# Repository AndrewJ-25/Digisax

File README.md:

# STARLITE

## Description
STARLITE is a minimalist Digital Saxophone (Digisax) controlled by ESP32-S3.

### Inspiration
This project is intended to be a cost effective, customisable alternative to commercially available wind synths. STARLITE can be used for both performance and silent practice. It weds my two favorite hobbies: music and tinkering.

### Features:
- realistic ergonomics
- UI in the form of an OLED display and rotary encoder, to control master volume and timbre
- differential pressure sensor for responsive breath control
- pressure tube and bleed tube to simulate realistic resistance to blowing
- audio synthesised locally
- 3x7 key matrix featuring MX Black switches
- power via 5V barrel jack
- DAC with headphone output

The neck can be blown into directly, but an alto saxophone mouthpiece is recommended. (Not included in this project.)

OnShape link: https://cad.onshape.com/documents/a64dba8dfd86a5efa1851173/w/8b62b2d00aa632cf961d9b4c/e/8ecfcb79b78c17c244b3f0aa

## Schematic and PCB

A pdf version can be found under pcb/unconnected_pcb.

PCB front

PCB back

NOTE: Kicad project contatining an unconnected, partially routed pcb can be found under pcb/unconnected_pcb. A fully routed, panelised pcb can be found under pcb/panelised_pcb. Gerber files were generated from the latter.

## Assembly
1. All parts can be handsoldered. I recommend soldering the key-switches last.
2. 3D printed parts to contain M3 heatset inserts.
3. Cut two lengths of food grade silicone tubing, 70mm (pressure tube) and 240mm (bleed tube) in length.
4. All plumbing is a push fit. Connect the pressure tube between the neck and pressure sensor. Bleed tube carries condensation from the neck to the bottom of the instrument. Holes in the right-hand-pinky-keys can hold the bleed tube in place.
5. All keycaps are a push fit. See images at bottom of page for correct placement.
6. Wrap cork around the neck to ensure an airtight fit with the mouthpiece.

3D printed parts:

|Quantity|Description|
|-|-|
|1|key B|
|1|key B-flat|
|1|key C-sharp|
|1|key G-sharp|
|3|key left palm|
|1|key low B flat|
|1|key Octave|
|3|key right palm|
|2|key right pinky|
|7|key round|
|1|mount left|
|1|mount left palm|
|1|mount left pinky|
|2|mount right palm|
|2|mount right pinky|

## BOM
|Quantity|Total cost/GBP|Description|MPN|Suggested source|
|-|-|-|-|-|
|1|16.88|PCB|-|https://jlcpcb.com/|
|1|6.30|DAC amplifier|Adafruit TLV320DAC3100 breakout board|https://thepihut.com/products/adafruit-tlv320dac3100-i2s-dac-with-headphone-and-speaker-out|
|1|10.40|MCU|ESP32-S3-DevKitC-1|https://www.aliexpress.com/item/1005009298826918.html|
|1|5.73|Differential pressure sensor|MPXV7007DP|https://www.aliexpress.com/item/1005009368234291.html|
|1|1.43|I2C ADC|MCP3221|https://www.mouser.co.uk/ProductDetail/Microchip-Technology/MCP3221A7T-E-OT?qs=uHi2%2FQoPa5B%2FLE1GKuvdgg%3D%3D|
|21|23.49 (30pcs)|Keyboard switches|Cherry MX Black|https://www.ebay.co.uk/itm/203537430495?_skw=mx+black+switch|
|1|3.80|0.91" OLED display|SSD1306|https://www.aliexpress.com/item/1005006365845676.html|
|1|1.16|rotary encoder|EC11|https://www.aliexpress.com/item/1005005983134515.html|
|1|0.80|Barrel jack|DC-005|https://www.aliexpress.com/item/4001206395694.html|
|21|2.27|Diode|1N4148|https://www.aliexpress.com/item/1005010526571917.html|
|4|3.00|Capacitors|470pF, 100nF, 470uF|https://www.digikey.co.uk/|
|29|5.75 (50 pcs)|Screw M3|M3 * 12 Phillip's head|https://www.ebay.co.uk/itm/221326204336|
|29|8.88 (100 pcs)|Heat-set insert M3|M3 * 4 * 4.5|https://www.ebay.co.uk/itm/376068195160|
|1|3.20|Food grade silicone hose|ID 3mm OD 5mm length 1mm|https://www.ebay.co.uk/itm/227352704780?var=526554578797|
|1|5.44|cork sheet|~2mm thickness|https://www.ebay.co.uk/itm/277911247699|
|-|10|3D printed parts|-|-|
|TOTAL|108.53|-|-|-|

## Code

Firmware is written in C++.

Column pins use the ESP-32's internal pullup, and all row pins are set to high. I implemented a loop where all the rows are pulled high by default, and any column which is detected as low is matched with the key's corresponding row.

At the moment the code detects simultaneous key presses and prints the note which the current fingering corresponds to. Matrix and fingering mappings can be found in the code/ directory.

Note synthesis and volume control via the rotary encoder will be implemented once the project is built.

```cpp
#include <Arduino.h>
#include <map>
#include <initializer_list>

// =====================
// MATRIX PINS
// =====================

int Rows[] = {7, 15, 16, 17, 18, 8, 9};
int Columns[] = {10, 11, 12};

// =====================
// KEY NAMES
// =====================

const char* saxKey[7][3] =
{
    {"Octave1","L1","Ls1"},
    {"fork1","Bf1","Ls2"},
    {"Rs1","L2","Ls3"},
    {"Rs2","L3","Gsh1"},
    {"Rs3","R1","Csh1"},
    {"Dsh1","R2","LB1"},
    {"C1","R3","LBf1"}
};

// =====================
// BIT POSITIONS
// =====================

enum KeyBits
{
    OCTAVE1,
    L1,
    LS1,
    FORK1,
    BF1,
    LS2,
    RS1,
    L2,
    LS3,
    RS2,
    L3,
    GSH1,
    RS3,
    R1,
    CSH1,
    DSH1,
    R2,
    LB1,
    C1,
    R3,
    LBF1
};

// =====================
// KEY -> BIT LOOKUP
// =====================

std::map<String, uint8_t> keyToBit =
{
    {"Octave1", OCTAVE1},
    {"L1", L1},
    {"Ls1", LS1},
    {"fork1", FORK1},
    {"Bf1", BF1},
    {"Ls2", LS2},
    {"Rs1", RS1},
    {"L2", L2},
    {"Ls3", LS3},
    {"Rs2", RS2},
    {"L3", L3},
    {"Gsh1", GSH1},
    {"Rs3", RS3},
    {"R1", R1},
    {"Csh1", CSH1},
    {"Dsh1", DSH1},
    {"R2", R2},
    {"LB1", LB1},
    {"C1", C1},
    {"R3", R3},
    {"LBf1", LBF1}
};

// =====================
// FINGERING TABLE
// =====================

std::map<uint32_t, float> waves;

// =====================
// CREATE BITMASK
// =====================

uint32_t makeMask(std::initializer_list<uint8_t> keys)
{
    uint32_t mask = 0;

    for(auto key : keys)
    {
        mask |= (1UL << key);
    }

    return mask;
}

// =====================
// SETUP
// =====================

void setup()
{
    Serial.begin(115200);

    // Row pins output
    for(int i = 0; i < 7; i++)
    {
        pinMode(Rows[i], OUTPUT);
        digitalWrite(Rows[i], HIGH);
    }

    // Column pins input pullup
    for(int i = 0; i < 3; i++)
    {
        pinMode(Columns[i], INPUT_PULLUP);
    }

    // =====================
    // NOTE TABLE
    // =====================

    waves[makeMask({L1,L2,L3,R1,R2,R3,C1,LBF1})] = 138.59;
    waves[makeMask({L1,L2,L3,R1,R2,R3,C1,LB1})]  = 146.83;
    waves[makeMask({L1,L2,L3,R1,R2,R3,C1})]      = 155.56;
    waves[makeMask({L1,L2,L3,R1,R2,R3,C1,CSH1})] = 164.81;
    waves[makeMask({L1,L2,L3,R1,R2,R3})]         = 174.61;
    waves[makeMask({L1,L2,L3,R1,R2,R3,DSH1})]    = 185.00;
    waves[makeMask({L1,L2,L3,R1,R2})]            = 196.00;
    waves[makeMask({L1,L2,L3,R1})]               = 207.65;
    waves[makeMask({L1,L2,L3,R2})]               = 220.00;
    waves[makeMask({L1,L2,L3})]                  = 233.08;
    waves[makeMask({L1,L2,L3,GSH1})]             = 246.94;
    waves[makeMask({L1,L2})]                     = 261.63;
    waves[makeMask({L1,BF1})]                    = 277.18;
    waves[makeMask({L1})]                        = 293.66;
    waves[makeMask({L2})]                        = 311.13;
    waves[makeMask({})]                          = 329.63;

    Serial.println("Digital Sax Ready");
}

// =====================
// LOOP
// =====================

void loop()
{
    uint32_t currentMask = 0;

    // Scan all rows
    for(int row = 0; row < 7; row++)
    {
        // Disable all rows
        for(int r = 0; r < 7; r++)
        {
            digitalWrite(Rows[r], HIGH);
        }

        // Activate one row
        digitalWrite(Rows[row], LOW);

        delayMicroseconds(50);

        // Read columns
        for(int col = 0; col < 3; col++)
        {
            if(digitalRead(Columns[col]) == LOW)
            {
                const char* keyName = saxKey[row][col];

                currentMask |=
                    (1UL << keyToBit[String(keyName)]);

                Serial.print("Pressed: ");
                Serial.println(keyName);
            }
        }
    }

    // Lookup note
    auto note = waves.find(currentMask);

    if(note != waves.end())
    {
        Serial.print("Frequency: ");
        Serial.println(note->second);
    }
    else
    {
        Serial.println("Unknown fingering");
    }

    Serial.println("----------------");

    delay(50);
}
```

## More images

## Acknowledgements <3

Massive thank you to Rehan for sacrificing his sleep to write the firmware.

Also to Sua for designing a BANGING zine.

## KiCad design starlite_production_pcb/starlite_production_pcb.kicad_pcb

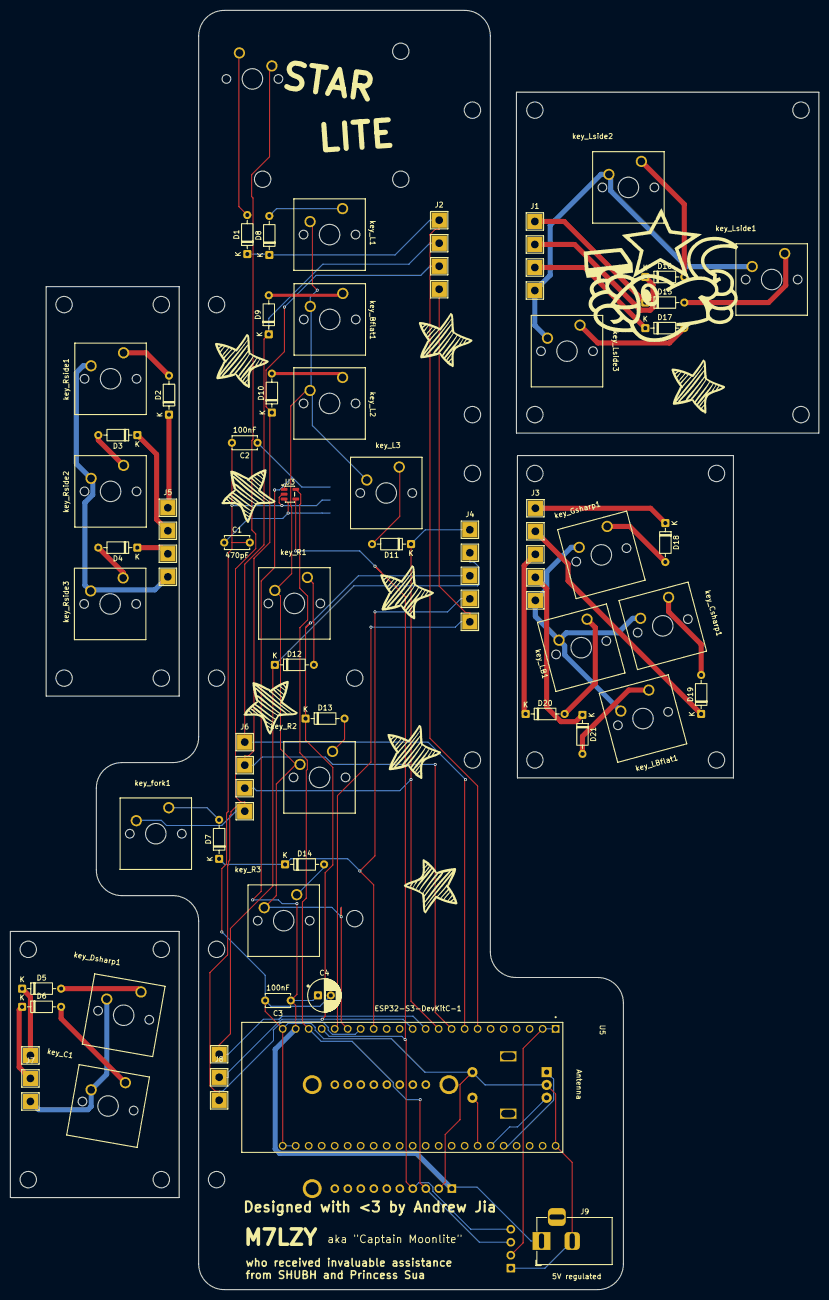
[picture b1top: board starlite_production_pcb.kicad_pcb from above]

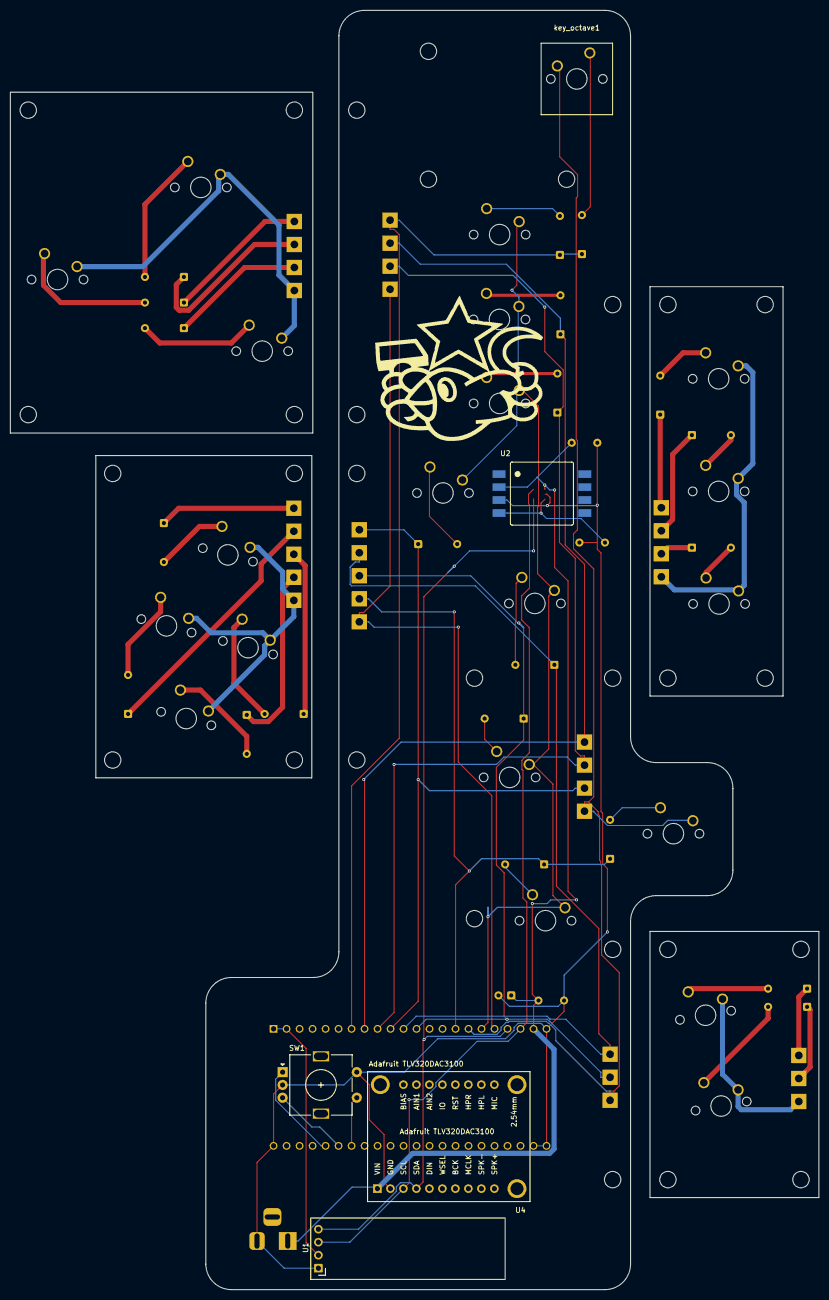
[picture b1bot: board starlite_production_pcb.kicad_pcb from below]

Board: 2 copper layers, 158.0 x 250.0 mm, 90 parts (5 on the bottom side), 56 nets.

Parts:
C1: 470pF; C_Disc_D4.7mm_W2.5mm_P5.00mm
C2, C3: 100nF; C_Disc_D4.7mm_W2.5mm_P5.00mm
C4: 470uF; CP_Radial_D6.3mm_P2.50mm
D1, D2, D3, D4, D5, D6, D7, D8, D9, D10, D11, D12, D13, D14, D15, D16, D17, D18, D19, D20, D21: 1N4148; D_DO-35_SOD27_P7.62mm_Horizontal
J1, J2, J5, J6: Conn_01x04_Pin; pad_1x4
J3, J4: Conn_01x05_Pin; pad_1x5
J7, J8: Conn_01x03_Pin; pad_1x3
J9: Barrel_Jack; BarrelJack_Horizontal
SW1: RotaryEncoder_Switch; RotaryEncoder_Alps_EC11E-Switch_Vertical_H20mm
U1: ER_OLEDM0.91_1x-I2C
U2: MPXV7007; MPXV7007DP
U3: MCP3221; SOT-23-5
U4: TLV320DAC3100_breakout; adafruit_TLV320DAC3100
U5: ESP32-S3; ESP32-S3-DevKitC-1
h1, h2, h3, h4, h5, h6, h7, h8, h9, h10, h11, h12, h13, h14, h16, h17, h18, h19, h20, h21, h22, h23, h24, h25: MountingHole_3.2mm_M3
key_Bflat1: SW_Push; slim_switch
key_C1: SW_Push; slim_switch
key_Csharp1: SW_Push; slim_switch
key_Dsharp1: SW_Push; slim_switch
key_Gsharp1: SW_Push; slim_switch
key_L1, key_L2, key_L3: SW_Push; slim_switch
key_LB1: SW_Push; slim_switch
key_LBflat1: SW_Push; slim_switch
key_Lside1, key_Lside2, key_Lside3: SW_Push; slim_switch
key_R1, key_R2, key_R3: SW_Push; slim_switch
key_Rside1, key_Rside2, key_Rside3: SW_Push; slim_switch
key_fork1: SW_Push; slim_switch
key_octave1: SW_Push; slim_switch
neck1, neck2, neck3: MountingHole_3.2mm_M3
thumb1, thumb2: MountingHole_3.2mm_M3

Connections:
+3.3V: U1.2 (VCC), U5.1 (3V3), U5.2 (3V3)
+5V: C2.1, C3.1, C4.1, J9.1, U2.2 (Vcc), U3.1 (V_{DD}), U4.1 (VIN), U5.21 (5V0)
EC11_A: SW1.A, U5.27 (GPIO2)
EC11_B: SW1.B, U5.28 (GPIO42)
EC11_button: SW1.S1, U5.29 (GPIO41)
GND: C1.2, C2.2, C3.2, C4.2, J9.2, SW1.C, SW1.S2, U1.1 (GND), U2.3 (GND), U3.2 (V_{SS}), U4.2 (GND), U5.22 (GND), U5.23 (GND), U5.43 (GND), U5.44 (GND)
I2C_SCL: U1.3 (SCL), U3.5 (SCL), U4.3 (SCL), U5.20 (GPIO14)
I2C_SDA: U1.4 (SDA), U3.4 (SDA), U4.4 (SDA), U5.19 (GPIO13)
unnamed: D1.2 (A), key_octave1.1
unnamed: D2.2 (A), key_Rside1.1
unnamed: D2.1 (K), J5.1
unnamed: D3.2 (A), key_Rside2.1
unnamed: D3.1 (K), J5.2
unnamed: D4.2 (A), key_Rside3.1
unnamed: D4.1 (K), J5.3
unnamed: D5.2 (A), key_Dsharp1.1
unnamed: D5.1 (K), J7.1
unnamed: D6.2 (A), key_C1.1
unnamed: D6.1 (K), J7.2
unnamed: D7.2 (A), key_fork1.1
unnamed: D8.2 (A), key_L1.1
unnamed: D9.2 (A), key_Bflat1.1
unnamed: D10.2 (A), key_L2.1
unnamed: D11.2 (A), key_L3.1
unnamed: D12.2 (A), key_R1.1
unnamed: D13.2 (A), key_R2.1
unnamed: D14.2 (A), key_R3.1
unnamed: D15.2 (A), key_Lside1.1
unnamed: D15.1 (K), J1.1
unnamed: D16.2 (A), key_Lside2.1
unnamed: D16.1 (K), J1.2
unnamed: D17.2 (A), key_Lside3.1
unnamed: D17.1 (K), J1.3
unnamed: D18.2 (A), key_Gsharp1.1
unnamed: D18.1 (K), J3.1
unnamed: D19.2 (A), key_Csharp1.1
unnamed: D19.1 (K), J3.2
unnamed: D20.2 (A), key_LB1.1
unnamed: D20.1 (K), J3.3
unnamed: D21.2 (A), key_LBflat1.1
unnamed: D21.1 (K), J3.4
unnamed: J1.4, key_Lside1.2, key_Lside2.2, key_Lside3.2
unnamed: J3.5, key_Csharp1.2, key_Gsharp1.2, key_LB1.2, key_LBflat1.2
unnamed: J5.4, key_Rside1.2, key_Rside2.2, key_Rside3.2
unnamed: J7.3, key_C1.2, key_Dsharp1.2
unnamed: C1.1, U2.4 (Vout), U3.3 (A_{IN})
key_col1: J6.4, J8.3, U5.16 (GPIO10), key_fork1.2, key_octave1.2
key_col2: U5.17 (GPIO11), key_Bflat1.2, key_L1.2, key_L2.2, key_L3.2, key_R1.2, key_R2.2, key_R3.2
key_col3: J2.4, J4.5, U5.18 (GPIO12)
key_row1: D1.1 (K), D8.1 (K), J2.1, U5.7 (GPIO7)
key_row2: D9.1 (K), J2.2, J6.1, U5.8 (GPIO15)
key_row3: D10.1 (K), J2.3, J6.2, U5.9 (GPIO16)
key_row4: D11.1 (K), J4.1, J6.3, U5.10 (GPIO17)
key_row5: D12.1 (K), J4.2, J8.1, U5.11 (GPIO18)
key_row6: D13.1 (K), J4.3, J8.2, U5.12 (GPIO8)
key_row7: D7.1 (K), D14.1 (K), J4.4, U5.15 (GPIO9)

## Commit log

2026-05-03 added gitignore
2026-05-16 symbols and shi
2026-05-16 uh idk what happened
2026-05-21 completed esp32 devboard symbol
2026-05-24 drew symbols for dac and manometer
2026-05-24 tidied up a bit
2026-06-01 started to added switches for keys
2026-06-02 added all switches, update symbols
2026-06-03 banished junk files
2026-06-03 added adc to schematic
2026-06-06 new DAC amp symbol
2026-06-06 banished
2026-06-06 added new dac to schem
2026-06-06 started matrix wiring
2026-06-08 completed first iteration of schem
2026-06-08 added decoupling caps
2026-06-09 custom dac footprint
2026-06-13 completed footprints and 3d models
2026-06-13 added all symbols :D
2026-06-13 new switch models.. yeah
2026-06-13 switch placement according to irl sax
2026-06-14 added headers to schem
2026-06-14 more kcal burnt on pcb
2026-06-15 added schematic pdf
2026-06-15 added pictures again?
2026-06-15 renamed dir
2026-06-15 exported jpeg
2026-06-15 fixed schematic labels
2026-06-15 updated schematic pdf
2026-06-15 created matrix map
2026-06-15 created fingering chart
2026-06-15 added barrel jack, sketched board outline
2026-06-15 had a go at routing
2026-06-15 routed central board in new kicad project
2026-06-16 Added the firmware to scan the matrix
    it gets the row and column being pressed
2026-06-16 Enhance README with code example and BOM
    Added code example for matrix scanning with ESP-32 and updated README with BOM details.
2026-06-16 added silkscreen art
2026-06-16 routed central board
2026-06-16 Ignore history directory
2026-06-16 saved again
2026-06-16 exported pcb step
2026-06-16 housekeeping
2026-06-17 created csv to replace txt
2026-06-17 rearranged to fix clearance and alignment
2026-06-17 routed new pcb
2026-06-17 the birds the word/ removed the bird
2026-06-17 added the bird
2026-06-18 added mouse bites to startlite_production_pcb
2026-06-18 Refactor key handling and add bitmask creation
    Refactor code to use std::map for key-to-bit lookup and improve readability. Added makeMask function for bitmask creation.
2026-06-18 Refactor matrix key scanning and note detection
    Refactor code for matrix key scanning and note detection. Improved handling of rows and columns, added key mapping and frequency output.
2026-06-19 update gitignore
2026-06-19 pcb render
2026-06-19 added gerbers
2026-06-19 exported step files
2026-06-19 modified neck
2026-06-19 banished chopped txt formatting
2026-06-19 vell this is awkward
2026-06-19 exported schematic as png
2026-06-19 added some pics
2026-06-19 exported stl
2026-06-19 exported zine
2026-06-19 created bom
2026-06-23 uploaded final_assembly.step
2026-06-23 screenshot pcb
2026-06-23 added CAD folder, exported schematic png from pdf
2026-06-23 moved schematic png
2026-06-23 exported better schematic png
2026-06-23 even better resolution png
2026-06-23 exportet as jpeg
2026-06-23 moved kicad files
2026-06-23 updated gitignore
2026-06-23 banished backups
2026-06-23 sua test
2026-06-23 evicted suas son
